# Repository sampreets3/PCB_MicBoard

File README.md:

# PCB_MicBoard
A microphone amplifier board, which utilizes electret microphones and an amplifier circuit. Can be used as input section for smart speaker.

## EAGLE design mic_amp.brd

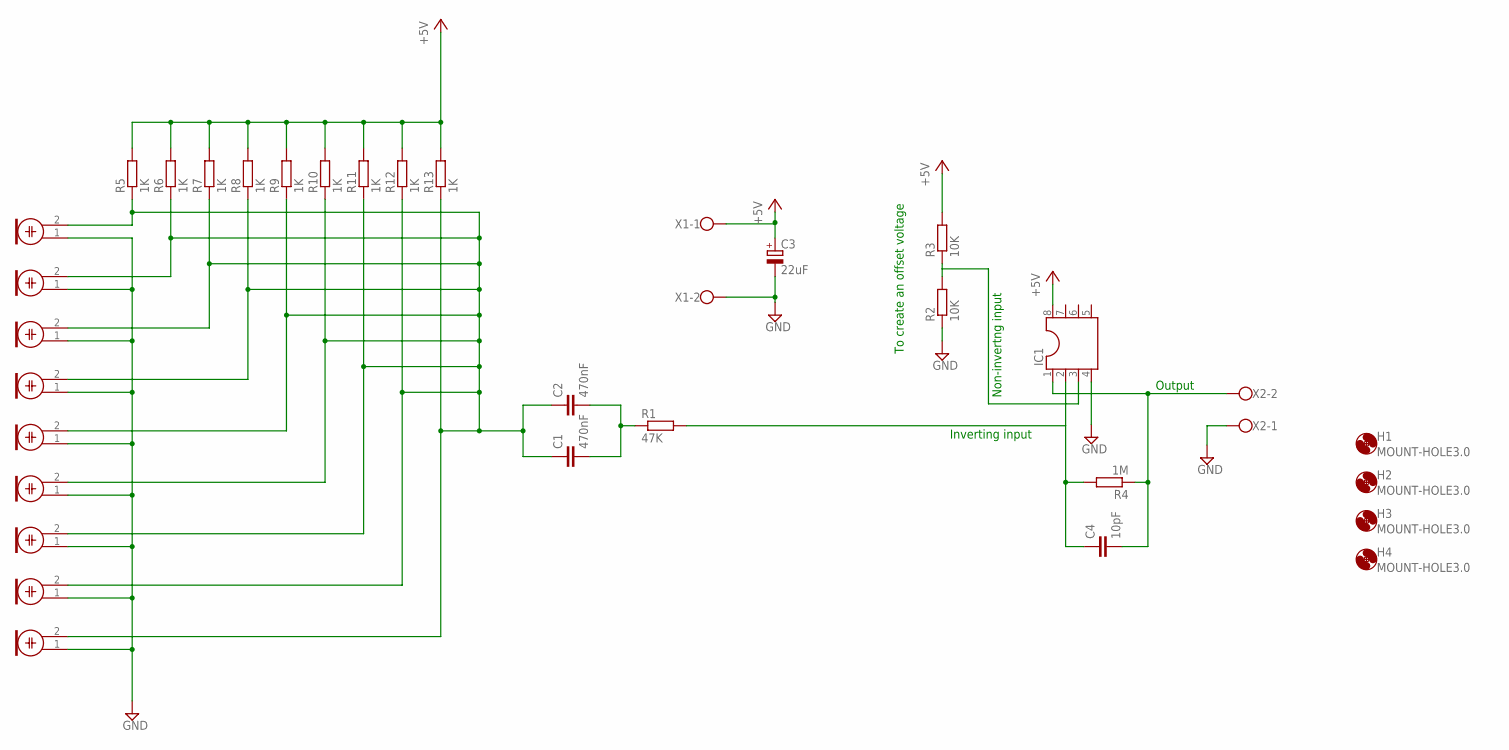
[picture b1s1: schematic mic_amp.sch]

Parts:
C1, C2: 470nF; C025-025X050
C3: 22uF; E2-5
C4: 10pF; C025-025X050
H1, H2, H3, H4: MOUNT-HOLE3.0; 3,0
IC1: DIL8S; SOCKET-08
M1, M2, M3, M4, M5, M6, M7, M8, M9: ELECTRET_MICROPHON-F6050AP; F6050AP
R1: 47K; 0207/10
R2, R3: 10K; 0207/10
R4: 1M; 0207/10
R5, R6, R7, R8, R9, R10, R11, R12, R13: 1K; 0207/10
X1, X2: W237-102

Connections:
+5V: C3.+, IC1.8, R3.2, R5.2, R6.2, R7.2, R8.2, R9.2, R10.2, R11.2, R12.2, R13.2, X1.1
GND: C3.-, IC1.4, M1.1, M2.1, M3.1, M4.1, M5.1, M6.1, M7.1, M8.1, M9.1, R2.1, X1.2, X2.1
unnamed: C4.1, IC1.2, R4.2
unnamed: C1.2, C2.2, R1.1
unnamed: IC1.3, R2.2, R3.1
unnamed: C1.1, C2.1, M1.2, M2.2, M3.2, M4.2, M5.2, M6.2, M7.2, M8.2, M9.2, R5.1, R6.1, R7.1, R8.1, R9.1, R10.1, R11.1, R12.1, R13.1
unnamed: C4.2, IC1.1, R4.1, X2.2

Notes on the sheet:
To create an offset voltage
Non-invertng input
Inverting input
Output

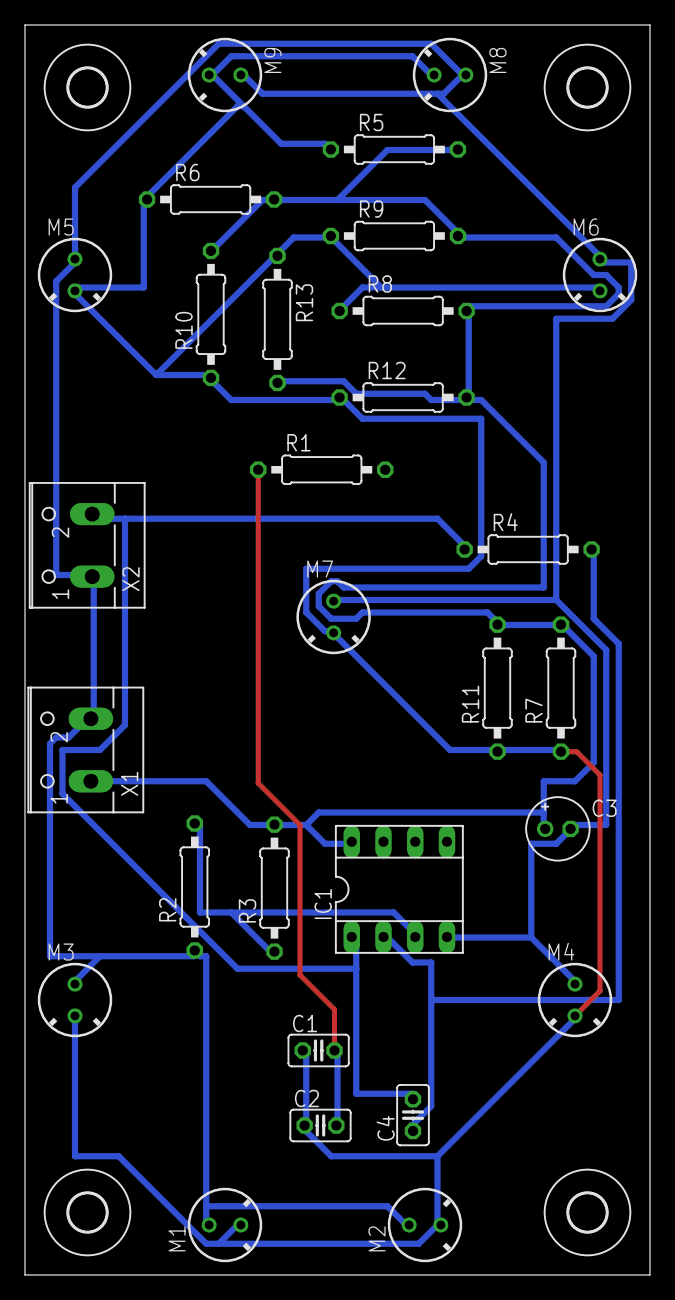
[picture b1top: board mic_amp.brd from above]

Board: 2 copper layers, 50.0 x 100.0 mm, 33 parts (0 on the bottom side), 7 nets.
